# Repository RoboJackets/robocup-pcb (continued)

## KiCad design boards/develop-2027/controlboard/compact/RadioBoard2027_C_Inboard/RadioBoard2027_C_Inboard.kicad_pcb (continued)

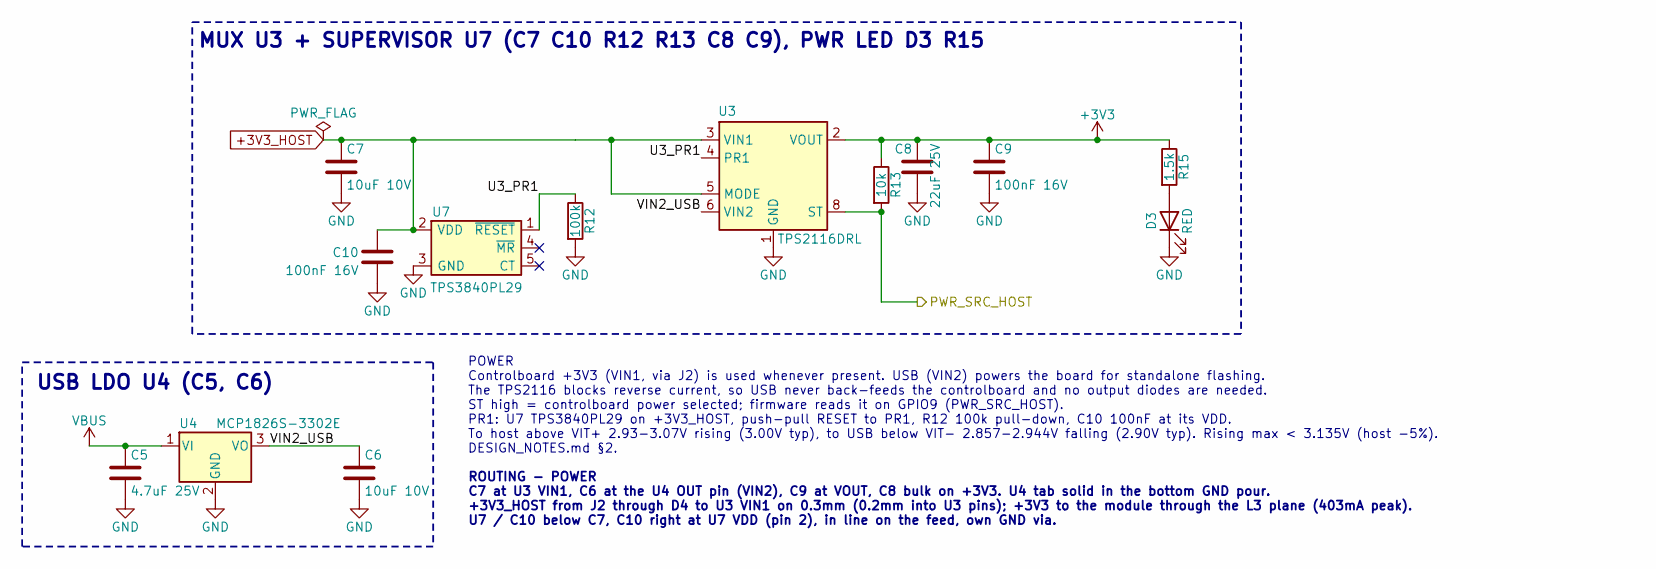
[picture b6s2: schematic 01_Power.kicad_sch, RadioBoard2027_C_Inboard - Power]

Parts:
C5: 4.7uF 25V; C_0805_2012Metric; Rating 25V X5R; MPN Samsung CL21A475KAQNNNE; LCSC C1779
C6, C7: 10uF 10V; C_0603_1608Metric; Rating 10V X5R 10%; MPN Samsung CL10A106KP8NNNC; LCSC C19702
C8: 22uF 25V; C_0805_2012Metric; Rating 25V X5R 20%; MPN Samsung CL21A226MAQNNNE; LCSC C45783
C9, C10: 100nF 16V; C_0402_1005Metric; Rating 16V X7R; MPN Samsung CL05B104KO5NNNC; LCSC C1525
D3: RED; LED_0603_1608Metric; MPN Kingbright APT1608EC; LCSC C5554143
R12: 100k; R_0402_1005Metric; Rating 1%; MPN UNI-ROYAL 0402WGF1003TCE; LCSC C25741
R13: 10k; R_0402_1005Metric; Rating 1%; MPN UNI-ROYAL 0402WGF1002TCE; LCSC C25744
R15: 1.5k; R_0402_1005Metric; Rating 1%; MPN UNI-ROYAL 0402WGF1501TCE; LCSC C25867
U3: TPS2116DRL; SOT-583-8; MPN TI TPS2116DRLR; LCSC C3235557
U4: MCP1826S-3302E; SOT-223-3_TabPin2; Rating 1A, VIN 6.0V max, 3.3V +-2.5%; MPN Microchip MCP1826S-3302E/DB; LCSC C638624
U7: TPS3840PL29; SOT-23-5; Rating VIT- 2.9V +-1.5%, VHYS 75-125mV, 10V VD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; MPN TI TPS3840PL29DBVR; LCSC C1852117

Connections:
+3V3: C8.1, C9.1, R13.1, R15.1, U3.2 (VOUT), U3.7 (VOUT); also elsewhere on the board
+3V3_HOST: C7.1, C10.1, U3.3 (VIN1), U3.5 (MODE), U7.2 (VDD); also elsewhere on the board
/ESP32-C5/PWR_SRC_HOST: R13.2, U3.8 (ST); also elsewhere on the board
/Power/U3_PR1: R12.1, U3.4 (PR1), U7.1 (~RESET)
/Power/VIN2_USB: C6.1, U3.6 (VIN2), U4.3 (VO)
GND: C5.2, C6.2, C7.2, C8.2, C9.2, C10.2, D3.1 (K), R12.2, U3.1 (GND), U4.2 (GND), U7.3 (GND); also elsewhere on the board
unnamed: D3.2 (A), R15.2
VBUS: C5.1, U4.1 (VI); also elsewhere on the board

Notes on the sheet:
MUX U3 + SUPERVISOR U7 (C7 C10 R12 R13 C8 C9), PWR LED D3 R15
USB LDO U4 (C5, C6)
POWER Controlboard +3V3 (VIN1, via J2) is used whenever present. USB (VIN2) powers the board for standalone flashing. The TPS2116 blocks reverse current, so USB never back-feeds the controlboard and no output diodes are needed. ST high = controlboard power selected; firmware reads it on GPIO9 (PWR_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
ROUTING - POWER C7 at U3 VIN1, C6 at the U4 OUT pin (VIN2), C9 at VOUT, C8 bulk on +3V3. U4 tab solid in the bottom GND pour. +3V3_HOST from J2 through D4 to U3 VIN1 on 0.3mm (0.2mm into U3 pins); +3V3 to the module through the L3 plane (403mA peak). U7 / C10 below C7, C10 right at U7 VDD (pin 2), 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

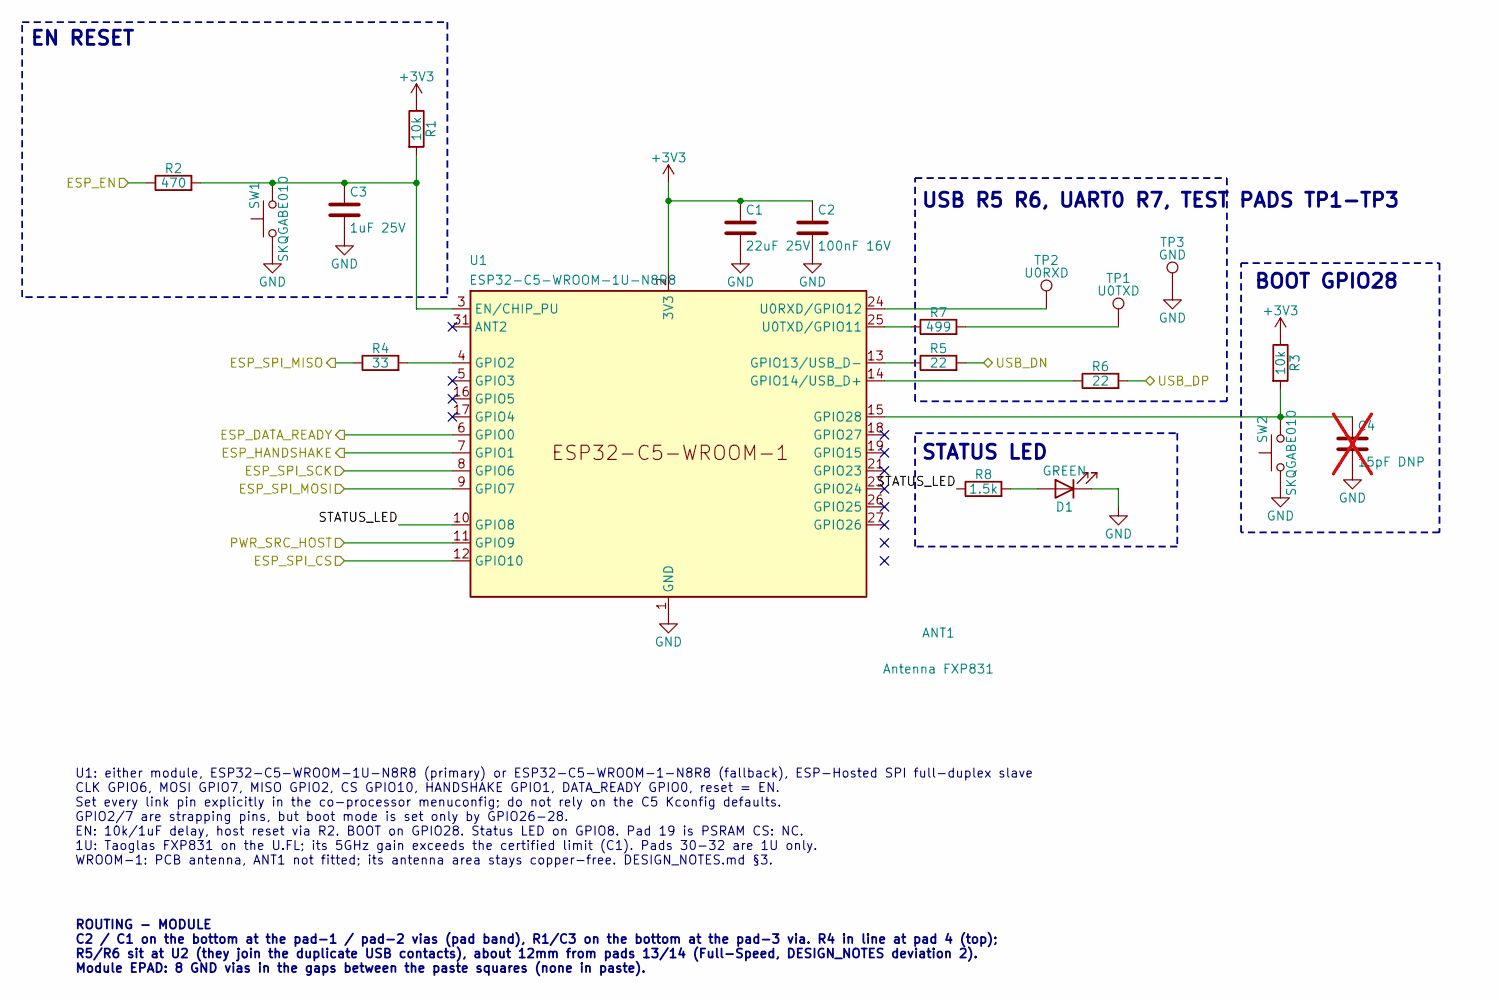
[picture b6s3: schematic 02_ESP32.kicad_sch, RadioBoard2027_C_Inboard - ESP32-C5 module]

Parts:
ANT1: Antenna FXP831; MPN Taoglas FXP831.07.0100C
C1: 22uF 25V; C_0805_2012Metric; Rating 25V X5R 20%; MPN Samsung CL21A226MAQNNNE; LCSC C45783
C2: 100nF 16V; C_0402_1005Metric; Rating 16V X7R; MPN Samsung CL05B104KO5NNNC; LCSC C1525
C3: 1uF 25V; C_0402_1005Metric; Rating 25V X5R; MPN Samsung CL05A105KA5NQNC; LCSC C52923
C4: 15pF DNP; C_0402_1005Metric; Rating 50V C0G; MPN Murata GRM1555C1H150JA01D; not fitted
D1: GREEN; LED_0603_1608Metric; MPN Kingbright APT1608SGC; LCSC C5875754
R1, R3: 10k; R_0402_1005Metric; Rating 1%; MPN UNI-ROYAL 0402WGF1002TCE; LCSC C25744
R2: 470; R_0402_1005Metric; Rating 1%; MPN UNI-ROYAL 0402WGF4700TCE; LCSC C25117
R4: 33; R_0402_1005Metric; Rating 1%; MPN UNI-ROYAL 0402WGF330JTCE; LCSC C25105
R5, R6: 22; R_0402_1005Metric; Rating 1%; MPN UNI-ROYAL 0402WGF220JTCE; LCSC C25092
R7: 499; R_0402_1005Metric; Rating 1%; MPN Yageo RC0402FR-07499RL; LCSC C137970
R8: 1.5k; R_0402_1005Metric; Rating 1%; MPN UNI-ROYAL 0402WGF1501TCE; LCSC C25867
SW1, SW2: SKQGABE010; SW_SPST_SKQG_WithStem; MPN Alps Alpine SKQGABE010; LCSC C115351
TP1: U0TXD; TestPoint_Pad_D1.0mm
TP2: U0RXD; TestPoint_Pad_D1.0mm
TP3: GND; TestPoint_Pad_D1.0mm
U1: ESP32-C5-WROOM-1U-N8R8; ESP32-C5-WROOM-1_1U_DUAL; MPN Espressif ESP32-C5-WROOM-1U-N8R8

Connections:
+3V3: C1.1, C2.1, R1.1, R3.1, U1.2 (3V3); also elsewhere on the board
/Controlboard Link/ESP_DATA_READY: U1.6 (GPIO0); also elsewhere on the board
/Controlboard Link/ESP_EN: R2.1; also elsewhere on the board
/Controlboard Link/ESP_HANDSHAKE: U1.7 (GPIO1); also elsewhere on the board
/Controlboard Link/ESP_SPI_CS: U1.12 (GPIO10); also elsewhere on the board
/Controlboard Link/ESP_SPI_MISO: R4.1; also elsewhere on the board
/Controlboard Link/ESP_SPI_MOSI: U1.9 (GPIO7); also elsewhere on the board
/Controlboard Link/ESP_SPI_SCK: U1.8 (GPIO6); also elsewhere on the board
/ESP32-C5/PWR_SRC_HOST: U1.11 (GPIO9); also elsewhere on the board
/ESP32-C5/STATUS_LED: R8.1, U1.10 (GPIO8)
/USB/USB_DN: R5.2; also elsewhere on the board
/USB/USB_DP: R6.2; also elsewhere on the board
GND: C1.2, C2.2, C3.2, C4.2, D1.1 (K), SW1.1, SW2.1, TP3.1, U1.1 (GND), U1.28 (GND), U1.29 (GND), U1.30 (GND), U1.32 (GND); also elsewhere on the board
unnamed: D1.2 (A), R8.2
unnamed: R7.2, TP1.1
unnamed: C3.1, R1.2, R2.2, SW1.2, U1.3 (EN/CHIP_PU)
unnamed: R4.2, U1.4 (GPIO2)
unnamed: R5.1, U1.13 (GPIO13/USB_D-)
unnamed: R6.1, U1.14 (GPIO14/USB_D+)
unnamed: C4.1, R3.2, SW2.2, U1.15 (GPIO28)
unnamed: TP2.1, U1.24 (U0RXD/GPIO12)
unnamed: R7.1, U1.25 (U0TXD/GPIO11)

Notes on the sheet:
EN RESET
USB R5 R6, UART0 R7, TEST PADS TP1-TP3
BOOT GPIO28
STATUS LED
ROUTING - MODULE C2 / C1 on the bottom at the pad-1 / pad-2 vias (pad band), R1/C3 on the bottom at the pad-3 via. R4 in line at pad 4 (top); R5/R6 sit at U2 (they join the duplicate USB contacts), about 12mm from pads 13/14 (Full-Speed, DESIGN_NOTES deviation 2). Module EPAD: 8 GND vias in the gap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
U1: either module, ESP32-C5-WROOM-1U-N8R8 (primary) or ESP32-C5-WROOM-1-N8R8 (fallback), ESP-Hosted SPI full-duplex slave CLK GPIO6, MOSI GPIO7, MISO GPIO2, CS GPIO10, HANDSHAKE GPIO1, DATA_READY GPIO0, reset = EN. Set every link pin explicitly in the co-processor menuconfig; do not rely on the C5 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

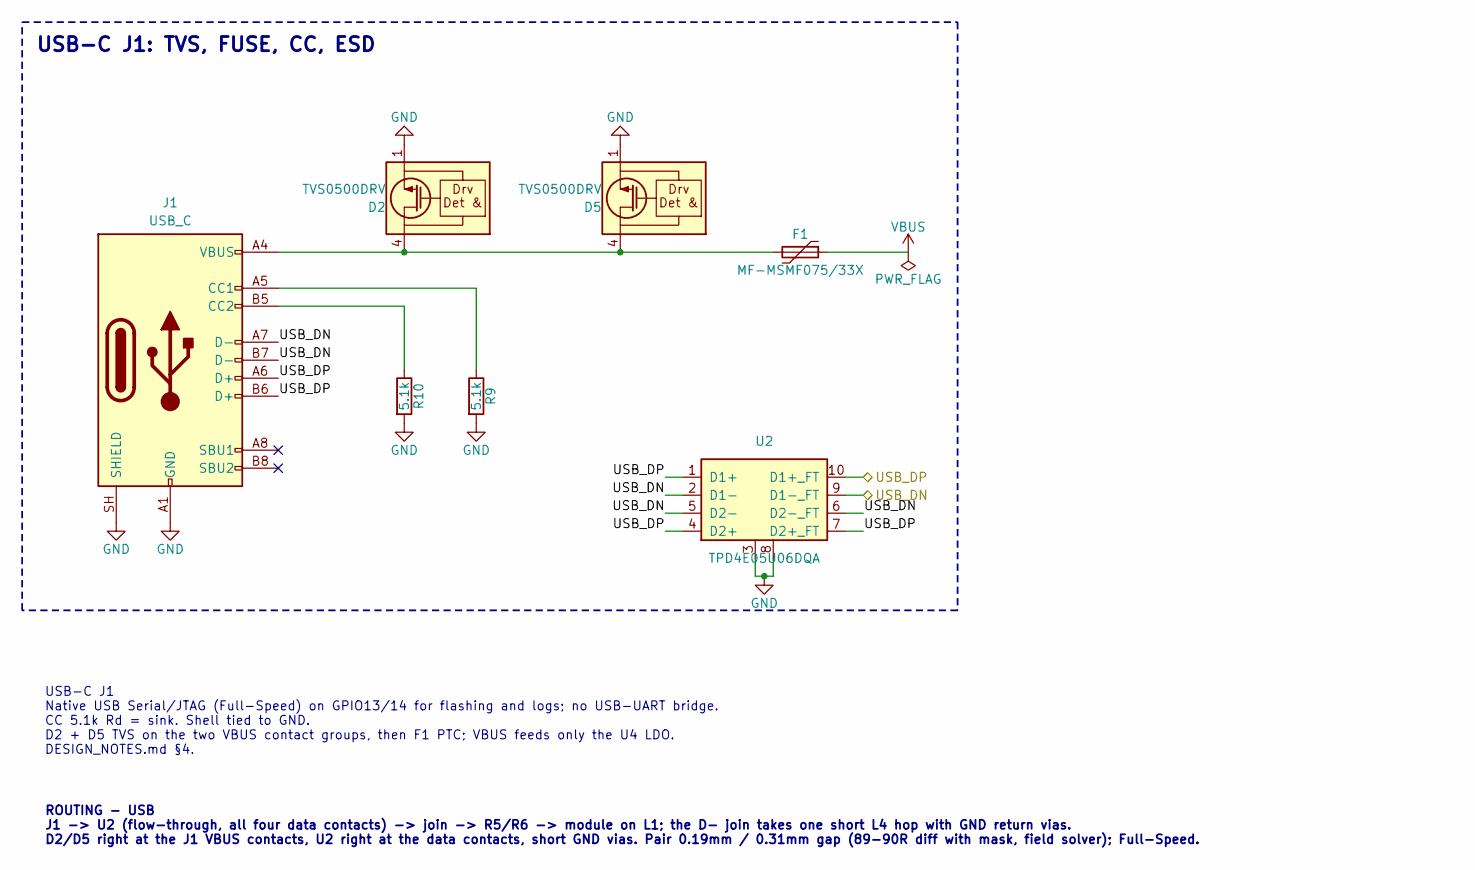
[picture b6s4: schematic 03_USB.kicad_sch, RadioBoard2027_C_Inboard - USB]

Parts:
D2, D5: TVS0500DRV; WSON-6-1EP_2x2mm_P0.65mm_EP1x1.6mm; MPN TI TVS0500DRVR; LCSC C609571
F1: MF-MSMF075/33X; Fuse_1812_4532Metric; Rating Hold 0.75A, trip 1.5A, 33V max, 1812; MPN Bourns MF-MSMF075/33X-2; LCSC C3760814
J1: USB_C; USB_C_Receptacle_GCT_USB4110; MPN GCT USB4110-GF-A; LCSC C5143397
R9, R10: 5.1k; R_0402_1005Metric; Rating 1%; MPN UNI-ROYAL 0402WGF5101TCE; LCSC C25905
U2: TPD4E05U06DQA; USON-10_2.5x1.0mm_P0.5mm; MPN TI TPD4E05U06DQAR; LCSC C138714

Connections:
/USB/USB_DN: J1.A7 (D-), J1.B7 (D-), U2.2 (D1-), U2.5 (D2-), U2.6 (D2-_FT), U2.9 (D1-_FT); also elsewhere on the board
/USB/USB_DP: J1.A6 (D+), J1.B6 (D+), U2.1 (D1+), U2.4 (D2+), U2.7 (D2+_FT), U2.10 (D1+_FT); also elsewhere on the board
GND: D2.1 (GND), D2.2 (GND), D2.3 (GND), D2.7 (GND), D5.1 (GND), D5.2 (GND), D5.3 (GND), D5.7 (GND), J1.A1 (GND), J1.A12 (GND), J1.B1 (GND), J1.B12 (GND), J1.SH (SHIELD), R9.2, R10.2, U2.3, U2.8; also elsewhere on the board
unnamed: D2.4 (IN), D2.5 (IN), D2.6 (IN), D5.4 (IN), D5.5 (IN), D5.6 (IN), F1.2, J1.A4 (VBUS), J1.A9 (VBUS), J1.B4 (VBUS), J1.B9 (VBUS)
unnamed: J1.A5 (CC1), R9.1
unnamed: J1.B5 (CC2), R10.1
VBUS: F1.1; also elsewhere on the board

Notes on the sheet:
USB-C J1: TVS, FUSE, CC, ESD
USB-C J1 Native USB Serial/JTAG (Full-Speed) on GPIO13/14 for flashing and logs; no USB-UART bridge. CC 5.1k Rd = sink. Shell tied to GND. D2 + D5 TVS on the two VBUS contact groups, then F1 PTC; VBUS feeds only the U4 LDO. DESIGN_NOTES.md §4.
ROUTING - USB J1 -> U2 (flow-through, all four data contacts) -> join -> R5/R6 -> module on L1; the D- join takes one short L4 hop with GND return vias. D2/D5 right at the J1 VBUS contacts, U2 right at the data contacts, short GND vias. Pair 0.19mm / 0.31mm gap (89-90R diff with mask, field solver)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

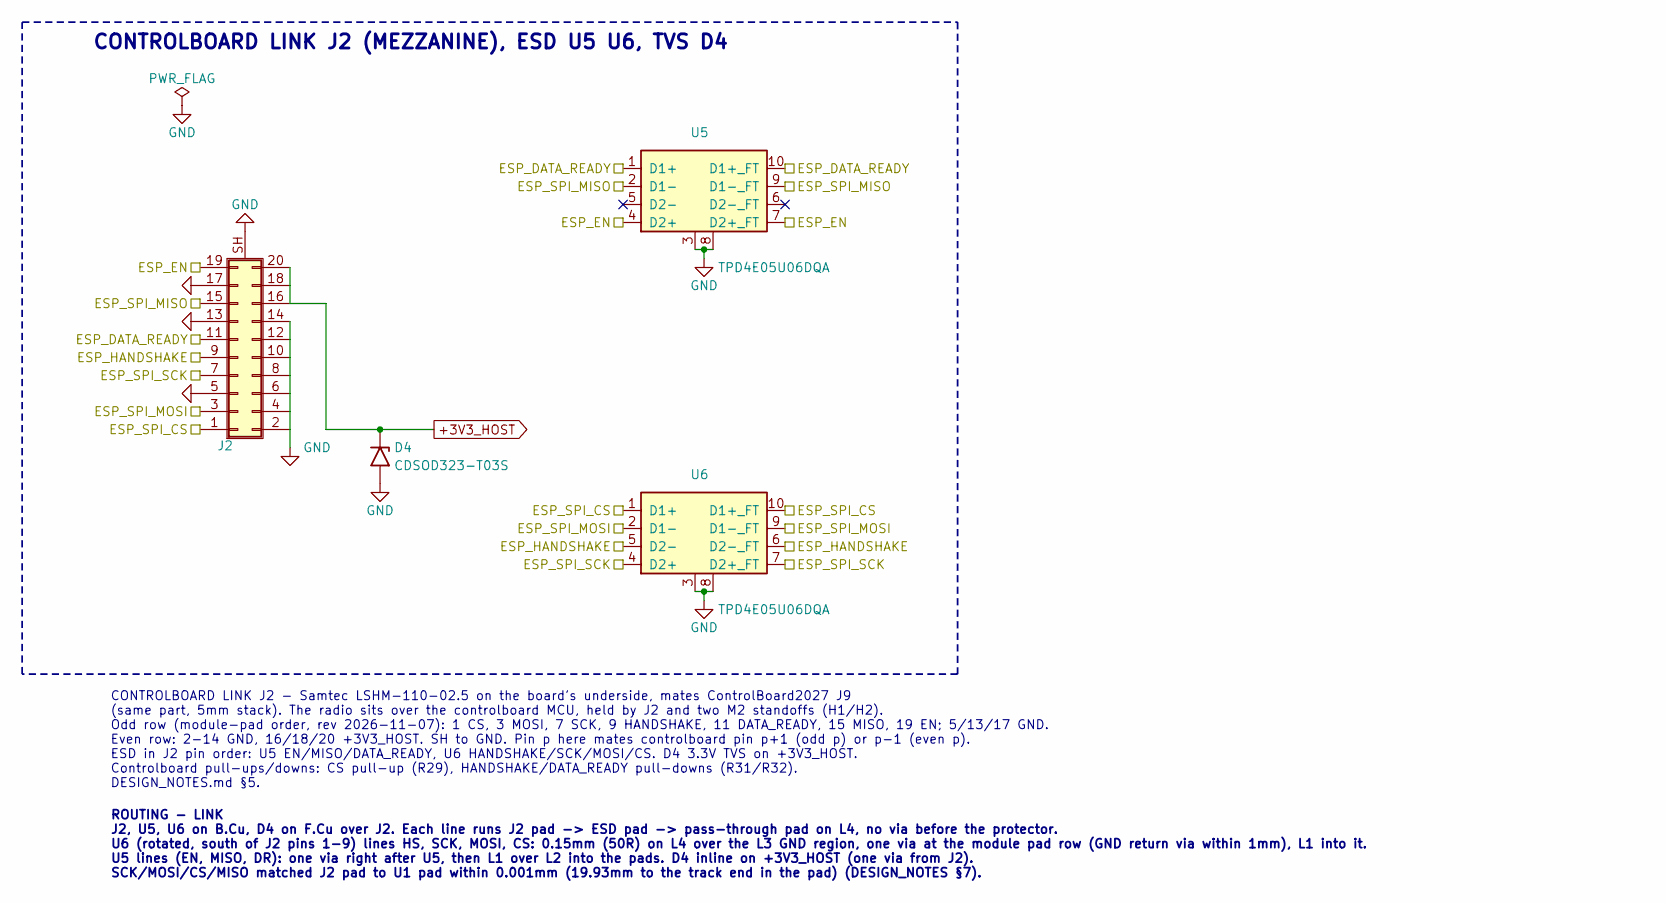
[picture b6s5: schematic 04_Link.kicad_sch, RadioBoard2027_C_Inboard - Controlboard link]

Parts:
D4: CDSOD323-T03S; D_SOD-323_Bourns; Rating 3.3V VRWM, 4.0V VBR min, 500W 8/20us; MPN Bourns CDSOD323-T03S; LCSC C3702214
J2: RADIO_MEZZ; Samtec_LSHM-110-xx.x-x-DV-S_2x10-1SH_P0.50mm_Vertical_PIH; MPN Samtec LSHM-110-02.5-L-DV-A-S-K-TR; LCSC C3643542
U5, U6: TPD4E05U06DQA; USON-10_2.5x1.0mm_P0.5mm; MPN TI TPD4E05U06DQAR; LCSC C138714

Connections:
+3V3_HOST: D4.1 (K), J2.16, J2.18, J2.20; also elsewhere on the board
/Controlboard Link/ESP_DATA_READY: J2.11, U5.1 (D1+), U5.10 (D1+_FT); also elsewhere on the board
/Controlboard Link/ESP_EN: J2.19, U5.4 (D2+), U5.7 (D2+_FT); also elsewhere on the board
/Controlboard Link/ESP_HANDSHAKE: J2.9, U6.5 (D2-), U6.6 (D2-_FT); also elsewhere on the board
/Controlboard Link/ESP_SPI_CS: J2.1, U6.1 (D1+), U6.10 (D1+_FT); also elsewhere on the board
/Controlboard Link/ESP_SPI_MISO: J2.15, U5.2 (D1-), U5.9 (D1-_FT); also elsewhere on the board
/Controlboard Link/ESP_SPI_MOSI: J2.3, U6.2 (D1-), U6.9 (D1-_FT); also elsewhere on the board
/Controlboard Link/ESP_SPI_SCK: J2.7, U6.4 (D2+), U6.7 (D2+_FT); also elsewhere on the board
GND: D4.2 (A), J2.2, J2.4, J2.5, J2.6, J2.8, J2.10, J2.12, J2.13, J2.14, J2.17, J2.SH (Shield), U5.3, U5.8, U6.3, U6.8; also elsewhere on the board

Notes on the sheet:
CONTROLBOARD LINK J2 (MEZZANINE), ESD U5 U6, TVS D4
CONTROLBOARD LINK J2 - Samtec LSHM-110-02.5 on the board's underside, mates ControlBoard2027 J9 (same part, 5mm stack). The radio sits over the controlboard MCU, held by J2 and two M2 standoffs (H1/H2). Odd row (module-pad order, rev 2026-11-07): 1 CS, 3 MOSI, 7 SCK, 9 HANDSHAKE, 11 DATA_READY, 15 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
ROUTING - LINK J2, U5, U6 on B.Cu, D4 on F.Cu over J2. Each line runs J2 pad -> ESD pad -> pass-through pad on L4, no via before the protector. U6 (rotated, south of J2 pins 1-9) lines HS, SCK, MOSI, CS: 0.15mm (50R) on L4 over the L3 GND region, one via at the module pad row (GND return via within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

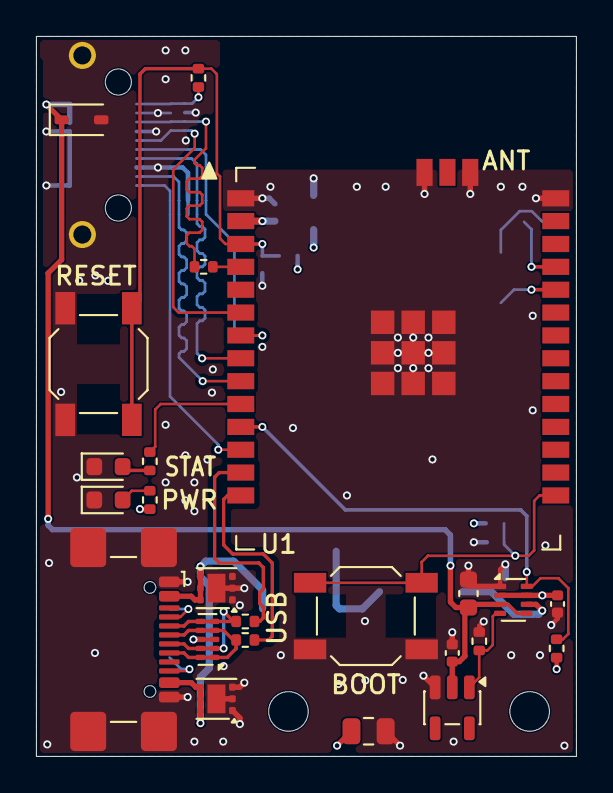
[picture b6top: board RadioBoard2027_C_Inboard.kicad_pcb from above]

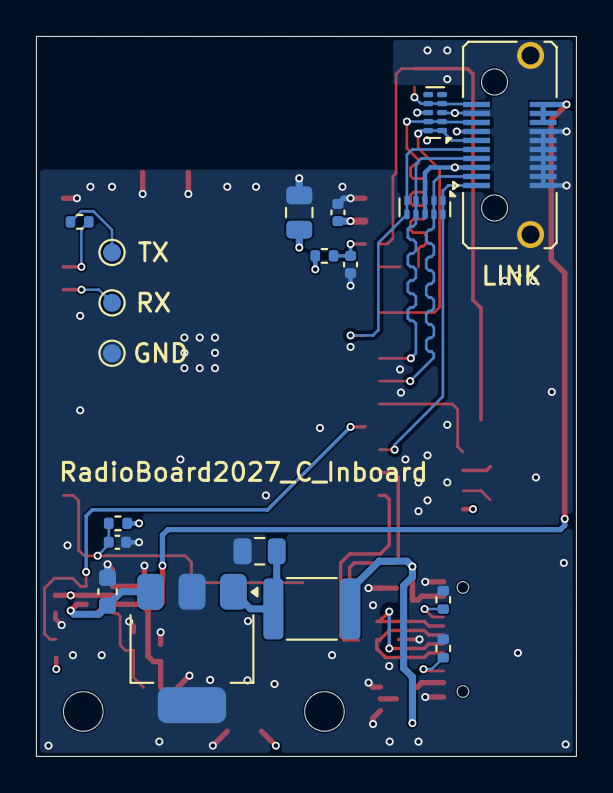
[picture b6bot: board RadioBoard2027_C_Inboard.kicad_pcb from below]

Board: 4 copper layers, 30.0 x 40.0 mm, 45 parts (19 on the bottom side), 30 nets.

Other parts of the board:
H1, H2: M2; MountingHole_2.2mm_M2

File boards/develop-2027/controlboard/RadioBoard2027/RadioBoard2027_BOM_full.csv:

Refs,Qty,Value,Footprint,MPN,Vendor PN,Rating
ANT1,1,Antenna FXP831,,Taoglas FXP831.07.0100C,931-1121-ND,
"C1,C8",2,22uF,Capacitor_SMD:C_0805_2012Metric,Samsung CL21A226MOQNNNE,1276-2909-1-ND,16V X5R 20%
"C2,C9",2,100nF,Capacitor_SMD:C_0402_1005Metric,Samsung CL05B104KO5NNNC,1276-1001-1-ND,16V X7R
C3,1,1uF,Capacitor_SMD:C_0402_1005Metric,Samsung CL05A105KA5NQNC,1276-1445-1-ND,25V X5R
C5,1,4.7uF,Capacitor_SMD:C_0805_2012Metric,TDK C2012X5R1E475K125AB,445-4116-1-ND,25V X5R
"C6,C7",2,10uF 10V,Capacitor_SMD:C_0603_1608Metric,Taiyo Yuden LMK107BBJ106MALT,587-3258-1-ND,10V X5R 20%
D1,1,GREEN,LED_SMD:LED_0603_1608Metric,Kingbright APT1608SGC,754-1121-1-ND,
"D2,D4",2,TVS0500DRV,Package_SON:WSON-6-1EP_2x2mm_P0.65mm_EP1x1.6mm,TI TVS0500DRVR,296-48382-1-ND,
D3,1,RED,LED_SMD:LED_0603_1608Metric,Kingbright APT1608EC,754-1117-1-ND,
F1,1,MF-MSMF075/33X,Fuse:Fuse_1812_4532Metric,Bourns MF-MSMF075/33X-2,118-MF-MSMF075/33X-2CT-ND,
J1,1,USB_C,Connector_USB:USB_C_Receptacle_GCT_USB4110,GCT USB4110-GF-A,2073-USB4110-GF-A-1-ND,
J2,1,RADIO_MEZZ,Connector_Samtec:Samtec_LSHM-110-xx.x-x-DV-S_2x10-1SH_P0.50mm_Vertical,Samtec LSHM-110-02.5-L-DV-A-S-K-TR,SAM14955CT-ND,
"R1,R3,R13",3,10k,Resistor_SMD:R_0402_1005Metric,Yageo RC0402FR-0710KL,311-10.0KLRCT-ND,1%
R2,1,470,Resistor_SMD:R_0402_1005Metric,Yageo RC0402FR-07470RL,311-470LRCT-ND,1%
R4,1,33,Resistor_SMD:R_0402_1005Metric,Yageo RC0402FR-0733RL,311-33.0LRCT-ND,1%
"R5,R6",2,22,Resistor_SMD:R_0402_1005Metric,Yageo RC0402FR-0722RL,311-22.0LRCT-ND,1%
R7,1,499,Resistor_SMD:R_0402_1005Metric,Yageo RC0402FR-07499RL,311-499LRCT-ND,1%
"R8,R15",2,1.5k,Resistor_SMD:R_0402_1005Metric,Panasonic ERJ-2RKF1501X,P1.50KLCT-ND,1%
"R9,R10",2,5.1k,Resistor_SMD:R_0402_1005Metric,Yageo RC0402FR-075K1L,311-5.10KLRCT-ND,1%
R11,1,100k,Resistor_SMD:R_0402_1005Metric,Yageo RC0402FR-07100KL,311-100KLRCT-ND,1%
R12,1,68k,Resistor_SMD:R_0402_1005Metric,Yageo RC0402FR-0768KL,311-68.0KLRCT-ND,1%
R14,1,1M,Resistor_SMD:R_0402_1005Metric,Yageo RC0402FR-071ML,311-1.00MLRCT-ND,1%
"SW1,SW2",2,SKQGABE010,Button_Switch_SMD:SW_SPST_SKQG_WithStem,Alps Alpine SKQGABE010,4809-SKQGABE010CT-ND,
U1,1,ESP32-C5-WROOM-1U-N8R8,RadioBoard2027:ESP32-C5-WROOM-1U,Espressif ESP32-C5-WROOM-1U-N8R8,356-ESP32C5WRM1UN8R8 (Mouser),
U2,1,USBLC6-2SC6,Package_TO_SOT_SMD:SOT-23-6,ST USBLC6-2SC6,497-5235-1-ND,
U3,1,TPS2116DRL,Package_TO_SOT_SMD:SOT-583-8,TI TPS2116DRLR,296-TPS2116DRLRCT-ND,
U4,1,AP7361C-33E,Package_TO_SOT_SMD:SOT-223-3_TabPin2,Diodes AP7361C-33E-13,AP7361C-33E-13DICT-ND,
"U5,U6",2,TPD4E05U06DQA,Package_SON:USON-10_2.5x1.0mm_P0.5mm,TI TPD4E05U06DQAR,296-35765-1-ND,

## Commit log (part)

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2026-04-10 ordered version 4-10-26
2026-04-30 remove unused submodules
2026-04-30 move inactive board to archive
2026-04-30 promote kicker-3.4 to mainline
2026-04-30 move modular motorboard to new scheme
2026-04-30 reorganize existing content to draft folder
2026-05-01 add skeleton
2026-05-01 Add schematic
2026-05-01 add AS5047 breakout board
2026-05-02 v1.1 - leave unused U/V floating instead of drive low
2026-05-02 add manufacturing notes for 1.1
2026-05-03 fix pcb formatting
2026-05-03 as5047p breakout test results
2026-05-03 Add application notes for AS5047P
2026-05-03 update magnet recommendation
2026-05-03 move obsidian vault for naming purposes
2026-05-05 notes from STSPIN32G0A2 datasheet
2026-05-05 Add application notes for power MOSFET
2026-05-05 Add notes from ST Application Notes
2026-05-05 Add reference materials for LM75A
2026-05-05 Application notes for LM75
2026-05-06 Add note about motor connectors
2026-05-07 Select shunt resistor
2026-05-07 select VBATT fuse
2026-05-08 Start on integration test board
2026-05-11 add results from more testing
2026-05-21 Add notes about motor connector part selection
2026-05-21 Add current sense, over-current circuits
2026-05-22 Add power stage
2026-05-22 Add test points
2026-05-24 Finish motor controller section
2026-05-25 Added power and connectors
2026-05-26 reformat root sheet, assign parts numbers for generics
2026-05-26 Set up PCB design rules
2026-06-30 remote sync
